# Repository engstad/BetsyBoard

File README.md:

# Experimental STM32L486 breakout board

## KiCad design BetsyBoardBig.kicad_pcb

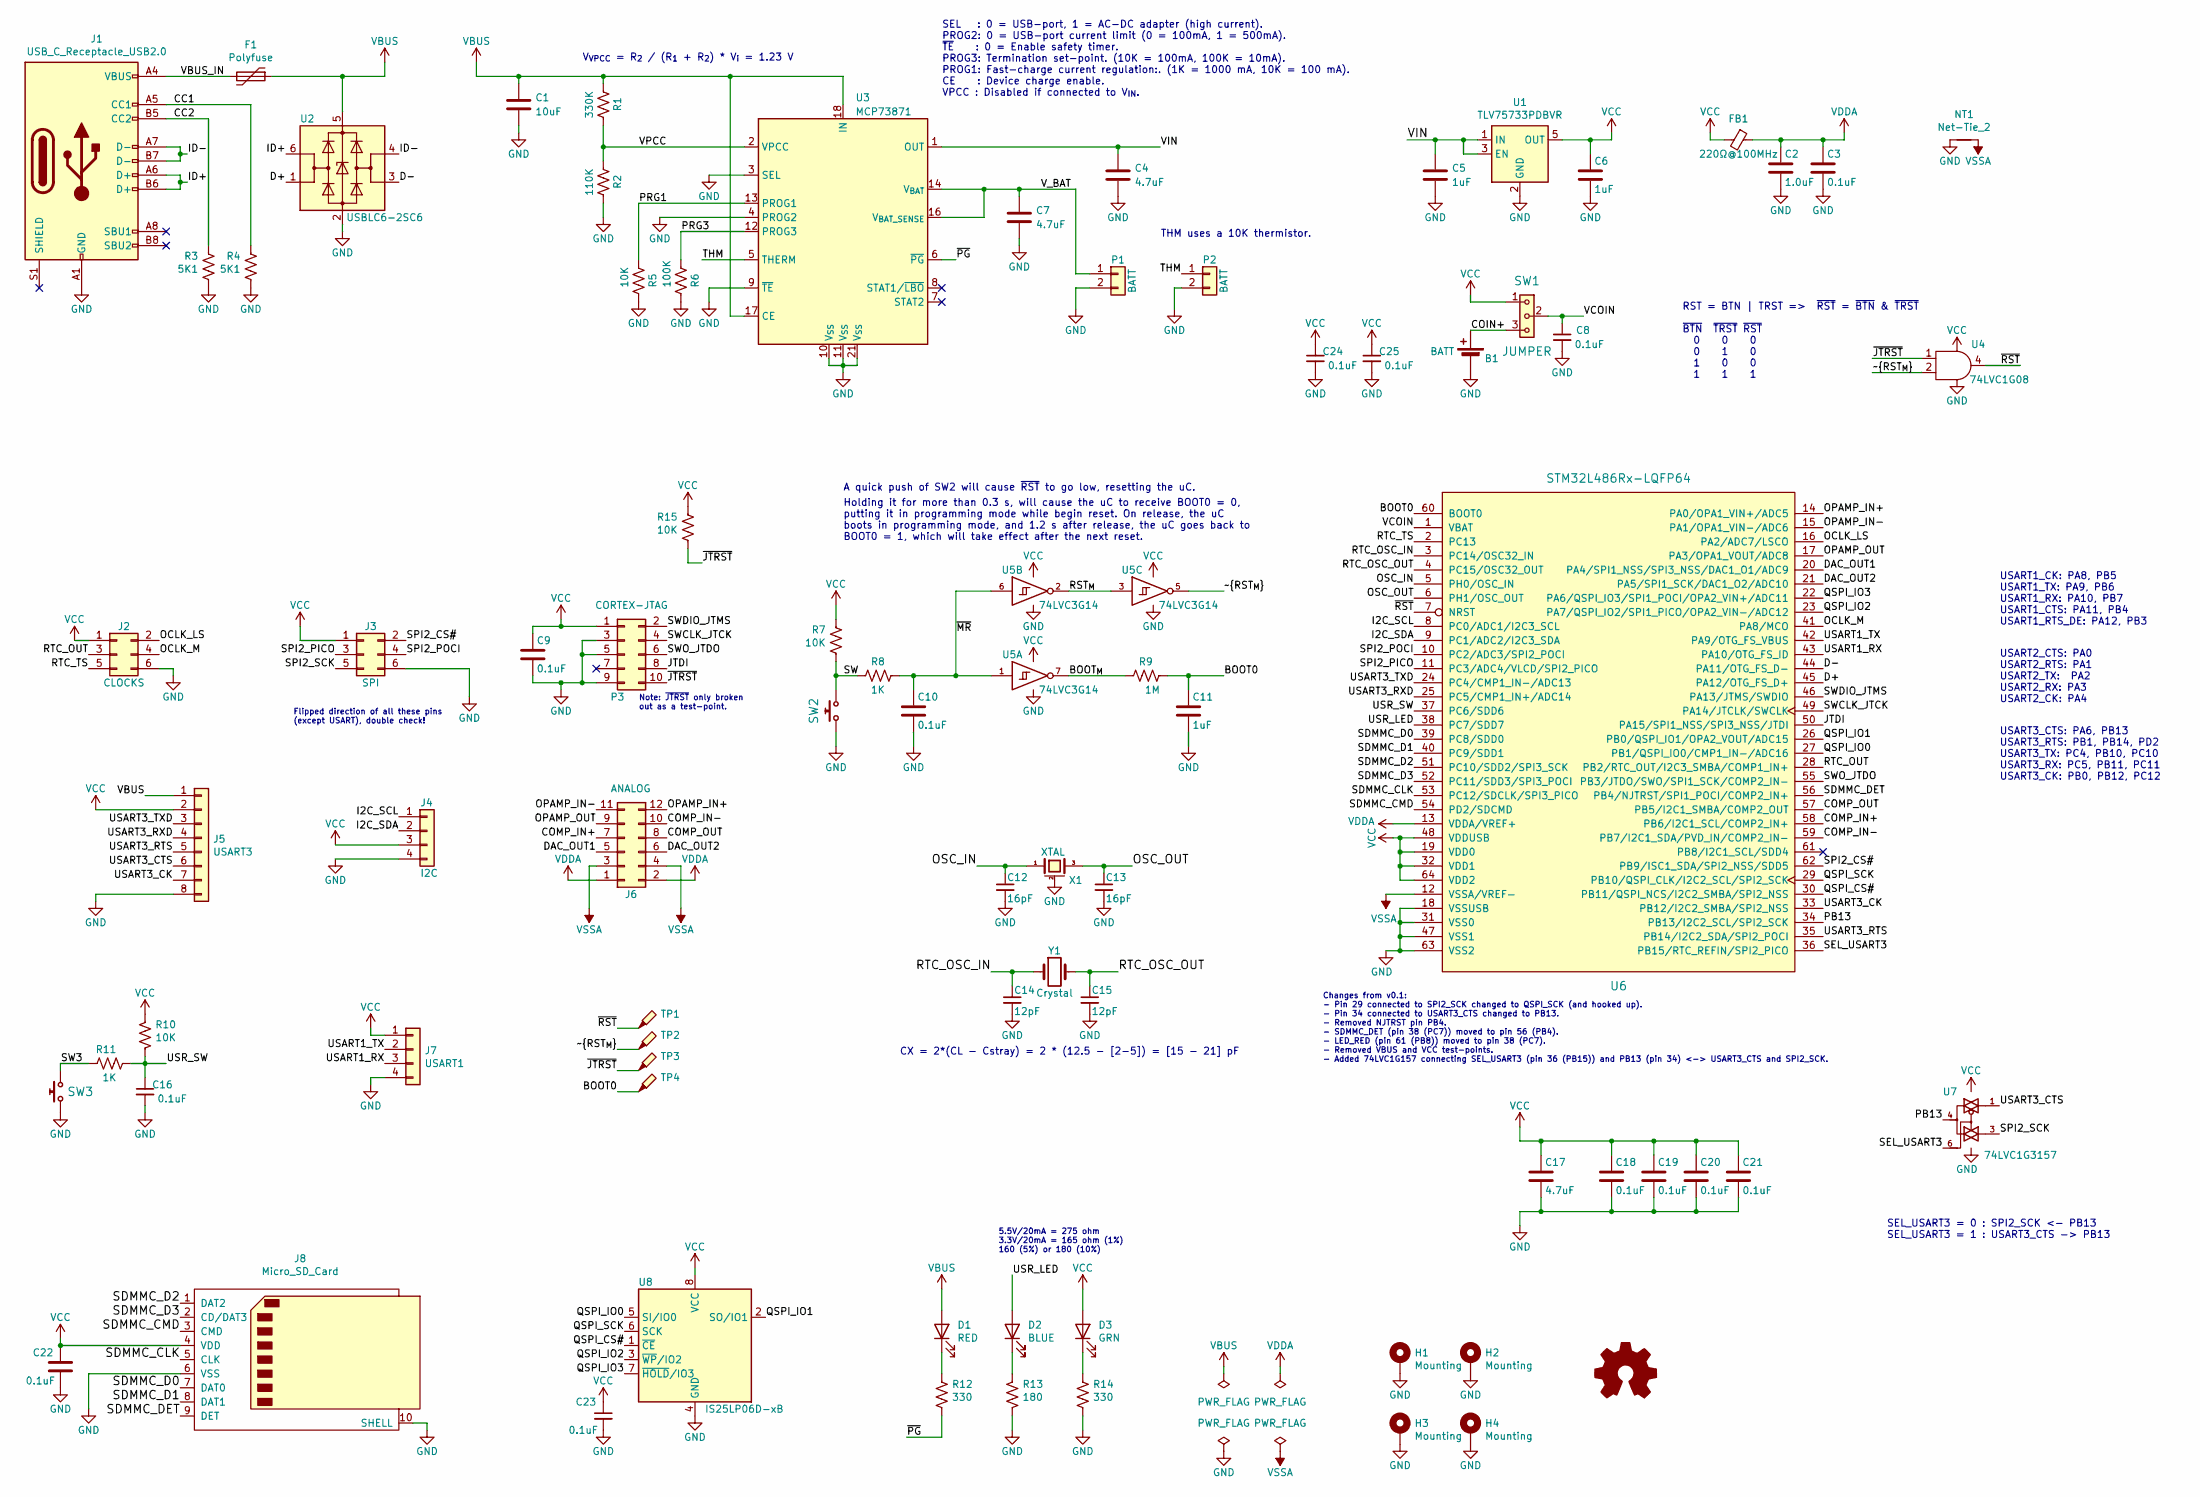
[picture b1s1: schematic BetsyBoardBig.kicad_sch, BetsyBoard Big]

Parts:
B1: BATT; Battery_Keystone_2894
C1: 10uF; C_0805_2012Metric
C2: 1.0uF; C_0805_2012Metric
C3, C8, C9, C10, C16, C18, C19, C20, C21, C22, C23, C24, C25: 0.1uF; C_0603_1608Metric
C4, C7, C17: 4.7uF; C_0805_2012Metric
C5, C6: 1uF; C_0805_2012Metric
C11: 1uF; C_0603_1608Metric
C12, C13: 16pF; C_0603_1608Metric
C14, C15: 12pF; C_0603_1608Metric
D1: RED; LED_0603_1608Metric
D2: BLUE; LED_0603_1608Metric
D3: GRN; LED_0603_1608Metric
F1: Polyfuse; Fuse_0805_2012Metric
FB1: 220Ω@100MHz; L_0805_2012Metric; Manuf # BLM21PG221SN1D
H1, H2, H3, H4: Mounting; MountingHole_3.2mm_M3_Pad_Via
J1: USB_C_Receptacle_USB2.0; USB_C_Receptacle_GCT_USB4085
J2: CLOCKS; PinHeader_2x03_P2.54mm_Vertical
J3: SPI; PinHeader_2x03_P2.54mm_Vertical
J4: I2C; JST_SH_SM04B-SRSS-TB_1x04-1MP_P1.00mm_Horizontal
J5: USART3; PinHeader_1x08_P2.54mm_Horizontal
J6: ANALOG; PinHeader_2x06_P2.54mm_Horizontal
J7: USART1; PinHeader_1x04_P2.54mm_Horizontal
J8: Micro_SD_Card; Molex_PS_105162_001; DigiKey# WM14405CT-ND
NT1: Net-Tie_2; NetTie-2_SMD_Pad0.5mm
P1: BATT; JST_PH_B2B-PH-K_1x02_P2.00mm_Vertical
P2: BATT; pin-socket-2
P3: CORTEX-JTAG; PinHeader_2x05_P1.27mm_Vertical
R1: 330K; R_0603_1608Metric
R2: 110K; R_0603_1608Metric
R3, R4: 5K1; R_0603_1608Metric
R5, R7, R10, R15: 10K; R_0603_1608Metric
R6: 100K; R_0603_1608Metric
R8, R11: 1K; R_0603_1608Metric
R9: 1M; R_0603_1608Metric
R12, R14: 330; R_0603_1608Metric
R13: 180; R_0603_1608Metric
SW1: JUMPER; PinHeader_1x03_P2.54mm_Vertical
SW2: TE-FSM4J; TACTILE_SWITCH-TE-FSM4JSMAATR
SW3: SW_PUSH_NO_ALT; TACTILE_SWITCH-TE-FSM4JSMAATR
TP1, TP2, TP3, TP4: TestPoint_Probe; TestPoint_Pad_1.0x1.0mm
U1: TLV75733PDBVR‎; SOT-23-5
U2: USBLC6-2SC6; SOT-23-6
U3: MCP73871; QFN-20-1EP_4x4mm_P0.5mm_EP2.5x2.5mm
U4: 74LVC1G08; SOT-23-5
U5: 74LVC3G14; SSOP-8_2.95x2.8mm_P0.65mm
U6: STM32L486Rx-LQFP64; LQFP-64_10x10mm_P0.5mm
U7: 74LVC1G3157; SOT-23-6
U8: IS25LP06D-xB; SOIC-8_5.275x5.275mm_P1.27mm
X1: XTAL; cstce-v-c
Y1: Crystal; Crystal_SMD_3215-2Pin_3.2x1.5mm

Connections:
/BOOT0: C11.1, R9.1, TP4.1, U6.60 (BOOT0)
/BOOT_{M}: R9.2, U5.7
/CC1: J1.A5 (CC1), R4.1
/CC2: J1.B5 (CC2), R3.1
/COIN+: B1.1 (+), SW1.3
/COMP_IN+: J6.7, U6.58 (PB6/I2C1_SCL/COMP2_IN+)
/COMP_IN-: J6.10, U6.59 (PB7/I2C1_SDA/PVD_IN/COMP2_IN-)
/COMP_OUT: J6.8, U6.57 (PB5/I2C1_SMBA/COMP2_OUT)
/D+: U2.1 (I/O1), U6.45 (PA12/OTG_FS_D+)
/D-: U2.3 (I/O2), U6.44 (PA11/OTG_FS_D-)
/DAC_OUT1: J6.5, U6.20 (PA4/SPI1_NSS/SPI3_NSS/DAC1_O1/ADC9)
/DAC_OUT2: J6.6, U6.21 (PA5/SPI1_SCK/DAC1_O2/ADC10)
/I2C_SCL: J4.1, U6.8 (PC0/ADC1/I2C3_SCL)
/I2C_SDA: J4.2, U6.9 (PC1/ADC2/I2C3_SDA)
/ID+: J1.A6 (D+), J1.B6 (D+), U2.6 (I/O1)
/ID-: J1.A7 (D-), J1.B7 (D-), U2.4 (I/O2)
/JTDI: P3.8, U6.50 (PA15/SPI1_NSS/SPI3_NSS/JTDI)
/OCLK_LS: J2.2, U6.16 (PA2/ADC7/LSCO)
/OCLK_M: J2.4, U6.41 (PA8/MCO)
/OPAMP_IN+: J6.12, U6.14 (PA0/OPA1_VIN+/ADC5)
/OPAMP_IN-: J6.11, U6.15 (PA1/OPA1_VIN-/ADC6)
/OPAMP_OUT: J6.9, U6.17 (PA3/OPA1_VOUT/ADC8)
/OSC_IN: C12.1, U6.5 (PH0/OSC_IN), X1.1
/OSC_OUT: C13.1, U6.6 (PH1/OSC_OUT), X1.3
/PB13: U6.34 (PB13/I2C2_SCL/SPI2_SCK), U7.4
/PRG1: R5.2, U3.13 (PROG1)
/PRG3: R6.2, U3.12 (PROG3)
/QSPI_CS#: U6.30 (PB11/QSPI_NCS/I2C2_SMBA/SPI2_NSS), U8.1 (~CE)
/QSPI_IO0: U6.27 (PB1/QSPI_IO0/CMP1_IN-/ADC16), U8.5 (SI/IO0)
/QSPI_IO1: U6.26 (PB0/QSPI_IO1/OPA2_VOUT/ADC15), U8.2 (SO/IO1)
/QSPI_IO2: U6.23 (PA7/QSPI_IO2/SPI1_PICO/OPA2_VIN-/ADC12), U8.3 (~WP/IO2)
/QSPI_IO3: U6.22 (PA6/QSPI_IO3/SPI1_POCI/OPA2_VIN+/ADC11), U8.7 (~HOLD/IO3)
/QSPI_SCK: U6.29 (PB10/QSPI_CLK/I2C2_SCL/SPI2_SCK), U8.6 (SCK)
/RST_{M}: U5.2, U5.3
/RTC_OSC_IN: C14.1, U6.3 (PC14/OSC32_IN), Y1.1
/RTC_OSC_OUT: C15.1, U6.4 (PC15/OSC32_OUT), Y1.2
/RTC_OUT: J2.3, U6.28 (PB2/RTC_OUT/I2C3_SMBA/COMP1_IN+)
/RTC_TS: J2.5, U6.2 (PC13)
/SDMMC_CLK: J8.5 (CLK), U6.53 (PC12/SDCLK/SPI3_PICO)
/SDMMC_CMD: J8.3 (CMD), U6.54 (PD2/SDCMD)
/SDMMC_D0: J8.7 (DAT0), U6.39 (PC8/SDD0)
/SDMMC_D1: J8.8 (DAT1), U6.40 (PC9/SDD1)
/SDMMC_D2: J8.1 (DAT2), U6.51 (PC10/SDD2/SPI3_SCK)
/SDMMC_D3: J8.2 (CD/DAT3), U6.52 (PC11/SDD3/SPI3_POCI)
/SDMMC_DET: J8.9 (DET), U6.56 (PB4/NJTRST/SPI1_POCI/COMP2_IN+)
/SEL_USART3: U6.36 (PB15/RTC_REFIN/SPI2_PICO), U7.6
/SPI2_CS#: J3.2, U6.62 (PB9/ISC1_SDA/SPI2_NSS/SDD5)
/SPI2_PICO: J3.3, U6.11 (PC3/ADC4/VLCD/SPI2_PICO)
/SPI2_POCI: J3.4, U6.10 (PC2/ADC3/SPI2_POCI)
/SPI2_SCK: J3.5, U7.3
/SW: R7.2, R8.2, SW2.2
/SW3: R11.2, SW3.2
/SWCLK_JTCK: P3.4, U6.49 (PA14/JTCLK/SWCLK)
/SWDIO_JTMS: P3.2, U6.46 (PA13/JTMS/SWDIO)
/SWO_JTDO: P3.6, U6.55 (PB3/JTDO/SWO/SPI1_SCK/COMP2_IN-)
/THM: P2.1, U3.5 (THERM)
/USART1_RX: J7.3, U6.43 (PA10/OTG_FS_ID)
/USART1_TX: J7.2, U6.42 (PA9/OTG_FS_VBUS)
/USART3_CK: J5.7, U6.33 (PB12/I2C2_SMBA/SPI2_NSS)
/USART3_CTS: J5.6, U7.1
/USART3_RTS: J5.5, U6.35 (PB14/I2C2_SDA/SPI2_POCI)
/USART3_RXD: J5.4, U6.25 (PC5/CMP1_IN+/ADC14)
/USART3_TXD: J5.3, U6.24 (PC4/CMP1_IN-/ADC13)
/USR_LED: D2.2 (A), U6.38 (PC7/SDD7)
/USR_SW: C16.1, R10.2, R11.1, U6.37 (PC6/SDD6)
/VBUS_IN: F1.2, J1.A4 (VBUS), J1.A9 (VBUS), J1.B4 (VBUS), J1.B9 (VBUS)
/VCOIN: C8.1, SW1.2, U6.1 (VBAT)
/VIN: C4.1, C5.1, U1.1 (IN), U1.3 (EN), U3.1 (OUT), U3.20 (OUT)
/VPCC: R1.1, R2.2, U3.2 (VPCC)
/V_BAT: C7.1, P1.1, U3.14 (V_{BAT}), U3.15 (V_{BAT}), U3.16 (V_{BAT_SENSE})
/~JTRST: P3.10, R15.2, TP3.1, U4.1
/~MR: C10.1, R8.1, U5.1, U5.6
/~PG: R12.2, U3.6 (~PG)
/~RST_{M}: TP2.1, U4.2, U5.5
/~RST: TP1.1, U4.4, U6.7 (NRST)
GND: B1.2 (-), C1.2, C2.2, C3.2, C4.2, C5.2, C6.2, C7.2, C8.2, C9.2, C10.2, C11.2, C12.2, C13.2, C14.2, C15.2, C16.2, C17.2, C18.2, C19.2, C20.2, C21.2, C22.2, C23.2, C24.2, C25.2, H1.1, H2.1, H3.1, H4.1, J1.A1 (GND), J1.A12 (GND), J1.B1 (GND), J1.B12 (GND), J2.6, J3.6, J4.4, J5.8, J7.4, J8.6 (VSS), J8.10 (SHELL), NT1.1, P1.2, P2.2, P3.3, P3.5, P3.9, R2.1, R3.2, R4.2, R5.1, R6.1, R13.2, R14.2, SW2.1, SW3.1, U1.2 (GND), U2.2 (GND), U3.3 (SEL), U3.4 (PROG2), U3.9 (~TE), U3.10 (V_{SS}), U3.11 (V_{SS}), U3.21 (V_{SS}), U4.3 (GND), U5.4 (GND), U6.18 (VSSUSB), U6.31 (VSS0), U6.47 (VSS1), U6.63 (VSS2), U7.2 (GND), U8.4 (GND), X1.2 (gnd)
unnamed: D1.1 (K), R12.1
unnamed: D2.1 (K), R13.1
unnamed: D3.1 (K), R14.1
VBUS: C1.1, D1.2 (A), F1.1, J5.1, R1.2, U2.5 (VBUS), U3.17 (CE), U3.18 (IN), U3.19 (IN)
VCC: C6.1, C9.1, C17.1, C18.1, C19.1, C20.1, C21.1, C22.1, C23.1, C24.1, C25.1, D3.2 (A), FB1.2, J2.1, J3.1, J4.3, J5.2, J7.1, J8.4 (VDD), P3.1, R7.1, R10.1, R15.1, SW1.1, U1.5 (OUT), U4.5 (VCC), U5.8 (VCC), U6.19 (VDD0), U6.32 (VDD1), U6.48 (VDDUSB), U6.64 (VDD2), U7.5 (VCC), U8.8 (VCC)
VDDA: C2.1, C3.1, FB1.1, J6.1, J6.2, U6.13 (VDDA/VREF+)
VSSA: J6.3, J6.4, NT1.2, U6.12 (VSSA/VREF-)

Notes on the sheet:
A quick push of SW2 will cause ~{RST} to go low, resetting the uC.
Note: ~{JTRST} only broken out as a test-point.
RST = BTN | TRST => ~{RST} = ~{BTN} & ~{TRST} ~{BTN} ~{TRST} ~{RST} 0 0 0 0 1 0 1 0 0 1 1 1
USART2_CTS: PA0 USART2_RTS: PA1 USART2_TX: PA2 USART2_RX: PA3 USART2_CK: PA4
Holding it for more than 0.3 s, will cause the uC to receive BOOT0 = 0, putting it in programming mode while begin reset. On release, the uC boots in programming mode, and 1.2 s after release, the uC goes back to BOOT0 = 1, which will take effect after the next reset.
Flipped direction of all these pins (except USART), double check!
THM uses a 10K thermistor.
CX = 2*(CL - Cstray) = 2 * (12.5 - [2-5]) = [15 - 21] pF
V_{VPCC} = R_{2} / (R_{1} + R_{2}) * V_{i} = 1.23 V
USART1_CK: PA8, PB5 USART1_TX: PA9, PB6 USART1_RX: PA10, PB7 USART1_CTS: PA11, PB4 USART1_RTS_DE: PA12, PB3
USART3_CTS: PA6, PB13 USART3_RTS: PB1, PB14, PD2 USART3_TX: PC4, PB10, PC10 USART3_RX: PC5, PB11, PC11 USART3_CK: PB0, PB12, PC12
SEL_USART3 = 0 : SPI2_SCK <- PB13 SEL_USART3 = 1 : USART3_CTS -> PB13
SEL : 0 = USB-port, 1 = AC-DC adapter (high current). PROG2: 0 = USB-port current limit (0 = 100mA, 1 = 500mA). ~{TE} : 0 = Enable safety timer. PROG3: Termination set-point. (10K = 100mA, 100K = 10mA). PROG1: Fast-charge current regulation:. (1K = 1000 mA, 10K = 100 mA). CE : Device charge enable.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
5.5V/20mA = 275 ohm 3.3V/20mA = 165 ohm (1%) 160 (5%) or 180 (10%)
Changes from v0.1: - Pin 29 connected to SPI2_SCK changed to QSPI_SCK (and hooked up). - Pin 34 connected to USART3_CTS changed to PB13. - Removed NJTRST pin PB4. - SDMMC_DET (pin 38 (PC7)) moved to pin 56 (PB4). - LED_RED (pin 61 (PB8)) moved to pin 38 (PC7). - Removed VBUS and VCC test-points. - 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

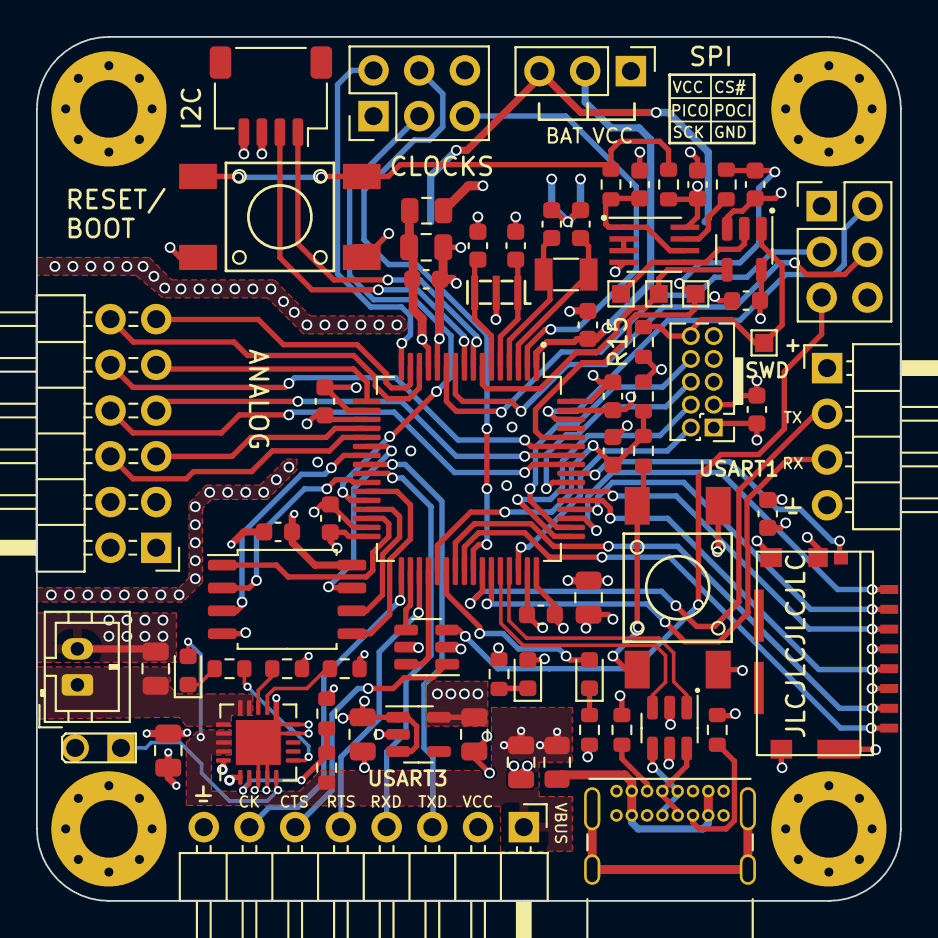
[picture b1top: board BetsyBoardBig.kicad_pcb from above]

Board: 4 copper layers, 48.0 x 48.0 mm, 79 parts (1 on the bottom side), 83 nets.

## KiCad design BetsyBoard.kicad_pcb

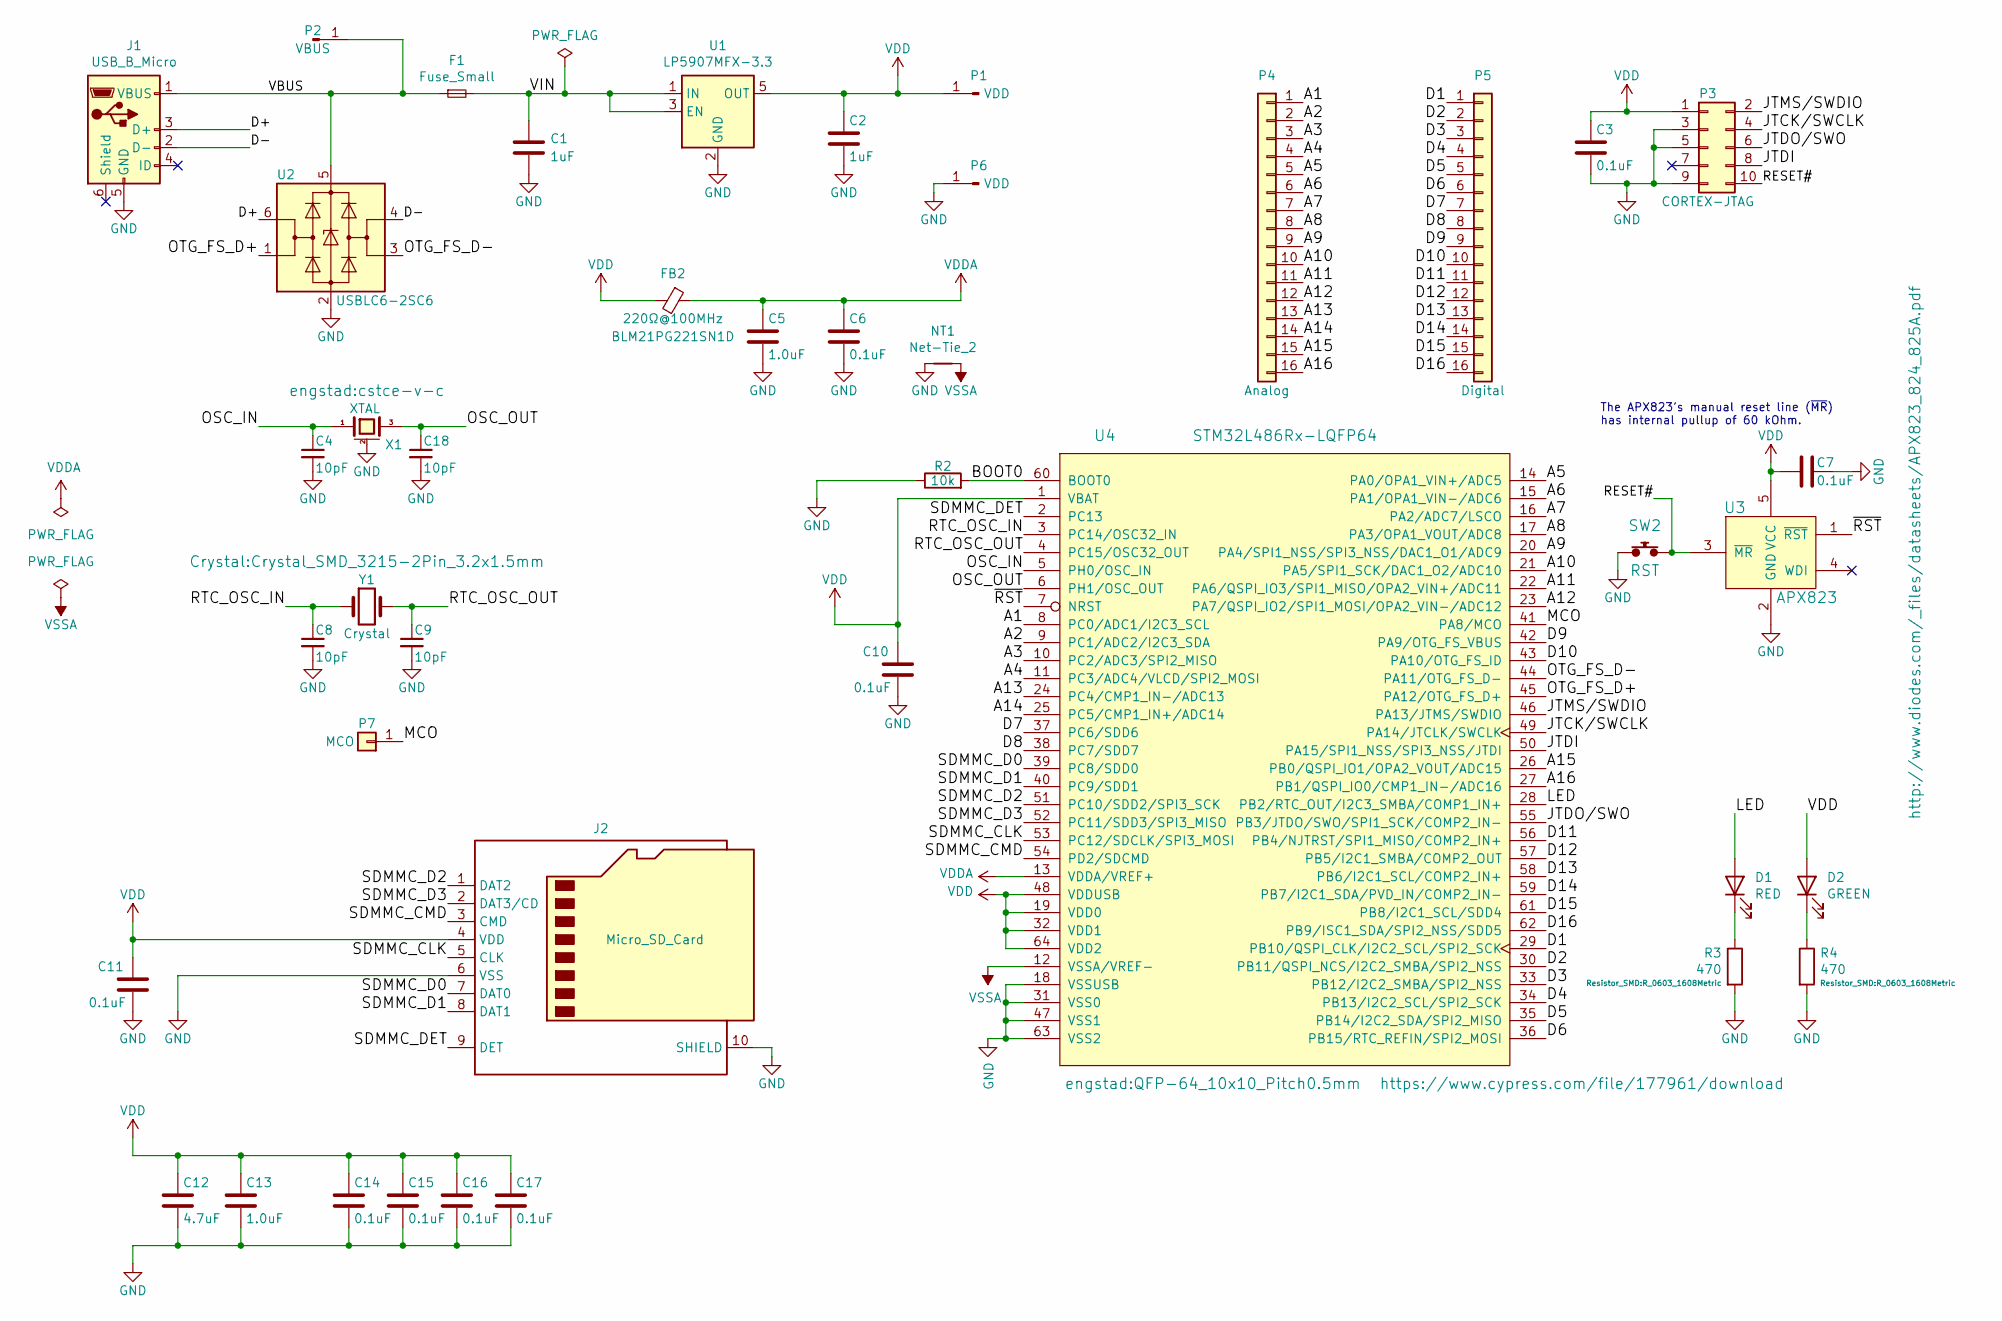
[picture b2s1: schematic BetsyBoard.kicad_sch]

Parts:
C1, C2: 1uF; C_0805_2012Metric
C3, C6, C7, C10, C11, C14, C15, C16, C17: 0.1uF; C_0603_1608Metric
C4, C8, C9, C18: 10pF; C_0603_1608Metric
C5: 1.0uF; C_0603_1608Metric
C12: 4.7uF; C_0805_2012Metric
C13: 1.0uF; C_0805_2012Metric
D1: RED; LED_0603_1608Metric
D2: GREEN; LED_0603_1608Metric
F1: Fuse_Small; Fuse_0805_2012Metric
FB2: 220Ω@100MHz; L_0805_2012Metric; Manuf # BLM21PG221SN1D
J1: USB_B_Micro; usb-micro-b-amphenol-fci-10118194-oval
J2: Micro_SD_Card; Molex_PS_105162_001
NT1: Net-Tie_2; net-tie-0.4mm
P1: VDD; pin-strip-1
P2: VBUS; pin-strip-1
P3: CORTEX-JTAG; conn-jtag-0.05; Mouser# 200-FTSH10501LDV007K
P4: Analog; pin-strip-16
P5: Digital; pin-strip-16
P6: VDD; PinHeader_1x01_P2.54mm_Vertical
P7: MCO; pin-socket-1
R2: 10k; R_0603_1608Metric
R3, R4: 470; R_0603_1608Metric
SW2: RST; tactile-switch-evpay-34x29mm
U1: LP5907MFX-3.3; SOT-23-5
U2: USBLC6-2SC6; SOT-23-6
U3: APX823; SOT-23-5
U4: STM32L486Rx-LQFP64; QFP-64_10x10_Pitch0.5mm
X1: XTAL; cstce-v-c
Y1: Crystal; Crystal_SMD_3215-2Pin_3.2x1.5mm

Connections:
/A1: P4.1, U4.8 (PC0/ADC1/I2C3_SCL)
/A2: P4.2, U4.9 (PC1/ADC2/I2C3_SDA)
/A3: P4.3, U4.10 (PC2/ADC3/SPI2_MISO)
/A4: P4.4, U4.11 (PC3/ADC4/VLCD/SPI2_MOSI)
/A5: P4.5, U4.14 (PA0/OPA1_VIN+/ADC5)
/A6: P4.6, U4.15 (PA1/OPA1_VIN-/ADC6)
/A7: P4.7, U4.16 (PA2/ADC7/LSCO)
/A8: P4.8, U4.17 (PA3/OPA1_VOUT/ADC8)
/A9: P4.9, U4.20 (PA4/SPI1_NSS/SPI3_NSS/DAC1_O1/ADC9)
/A10: P4.10, U4.21 (PA5/SPI1_SCK/DAC1_O2/ADC10)
/A11: P4.11, U4.22 (PA6/QSPI_IO3/SPI1_MISO/OPA2_VIN+/ADC11)
/A12: P4.12, U4.23 (PA7/QSPI_IO2/SPI1_MOSI/OPA2_VIN-/ADC12)
/A13: P4.13, U4.24 (PC4/CMP1_IN-/ADC13)
/A14: P4.14, U4.25 (PC5/CMP1_IN+/ADC14)
/A15: P4.15, U4.26 (PB0/QSPI_IO1/OPA2_VOUT/ADC15)
/A16: P4.16, U4.27 (PB1/QSPI_IO0/CMP1_IN-/ADC16)
/BOOT0: R2.2, U4.60 (BOOT0)
/D1: P5.1, U4.29 (PB10/QSPI_CLK/I2C2_SCL/SPI2_SCK)
/D2: P5.2, U4.30 (PB11/QSPI_NCS/I2C2_SMBA/SPI2_NSS)
/D3: P5.3, U4.33 (PB12/I2C2_SMBA/SPI2_NSS)
/D4: P5.4, U4.34 (PB13/I2C2_SCL/SPI2_SCK)
/D5: P5.5, U4.35 (PB14/I2C2_SDA/SPI2_MISO)
/D6: P5.6, U4.36 (PB15/RTC_REFIN/SPI2_MOSI)
/D7: P5.7, U4.37 (PC6/SDD6)
/D8: P5.8, U4.38 (PC7/SDD7)
/D9: P5.9, U4.42 (PA9/OTG_FS_VBUS)
/D10: P5.10, U4.43 (PA10/OTG_FS_ID)
/D11: P5.11, U4.56 (PB4/NJTRST/SPI1_MISO/COMP2_IN+)
/D12: P5.12, U4.57 (PB5/I2C1_SMBA/COMP2_OUT)
/D13: P5.13, U4.58 (PB6/I2C1_SCL/COMP2_IN+)
/D14: P5.14, U4.59 (PB7/I2C1_SDA/PVD_IN/COMP2_IN-)
/D15: P5.15, U4.61 (PB8/I2C1_SCL/SDD4)
/D16: P5.16, U4.62 (PB9/ISC1_SDA/SPI2_NSS/SDD5)
/D+: J1.3 (D+), U2.6 (I/O1)
/D-: J1.2 (D-), U2.4 (I/O2)
/JTCK/SWCLK: P3.4, U4.49 (PA14/JTCLK/SWCLK)
/JTDI: P3.8, U4.50 (PA15/SPI1_NSS/SPI3_NSS/JTDI)
/JTDO/SWO: P3.6, U4.55 (PB3/JTDO/SWO/SPI1_SCK/COMP2_IN-)
/JTMS/SWDIO: P3.2, U4.46 (PA13/JTMS/SWDIO)
/LED: D1.2 (A), U4.28 (PB2/RTC_OUT/I2C3_SMBA/COMP1_IN+)
/MCO: P7.1, U4.41 (PA8/MCO)
/OSC_IN: C4.1, U4.5 (PH0/OSC_IN), X1.1
/OSC_OUT: C18.1, U4.6 (PH1/OSC_OUT), X1.3
/OTG_FS_D+: U2.1 (I/O1), U4.45 (PA12/OTG_FS_D+)
/OTG_FS_D-: U2.3 (I/O2), U4.44 (PA11/OTG_FS_D-)
/RESET#: P3.10, SW2.2, U3.3 (~MR)
/RTC_OSC_IN: C8.1, U4.3 (PC14/OSC32_IN), Y1.1
/RTC_OSC_OUT: C9.1, U4.4 (PC15/OSC32_OUT), Y1.2
/SDMMC_CLK: J2.5 (CLK), U4.53 (PC12/SDCLK/SPI3_MOSI)
/SDMMC_CMD: J2.3 (CMD), U4.54 (PD2/SDCMD)
/SDMMC_D0: J2.7 (DAT0), U4.39 (PC8/SDD0)
/SDMMC_D1: J2.8 (DAT1), U4.40 (PC9/SDD1)
/SDMMC_D2: J2.1 (DAT2), U4.51 (PC10/SDD2/SPI3_SCK)
/SDMMC_D3: J2.2 (DAT3/CD), U4.52 (PC11/SDD3/SPI3_MISO)
/SDMMC_DET: J2.9 (DET), U4.2 (PC13)
/VBUS: F1.1, J1.1 (VBUS), P2.1, U2.5 (VBUS)
/VIN: C1.1, F1.2, U1.1 (IN), U1.3 (EN)
/~RST: U3.1 (~RST), U4.7 (NRST)
GND: C1.2, C2.2, C3.2, C4.2, C5.2, C6.2, C7.1, C8.2, C9.2, C10.2, C11.2, C12.2, C13.2, C14.2, C15.2, C16.2, C17.2, C18.2, J1.5 (GND), J2.6 (VSS), J2.10 (SHIELD), NT1.1, P3.3, P3.5, P3.9, P6.1, R2.1, R3.2, R4.2, SW2.1, U1.2 (GND), U2.2 (GND), U3.2 (GND), U4.18 (VSSUSB), U4.31 (VSS0), U4.47 (VSS1), U4.63 (VSS2), X1.2 (gnd)
unnamed: D1.1 (K), R3.1
unnamed: D2.1 (K), R4.1
VDD: C2.1, C3.1, C7.2, C10.1, C11.1, C12.1, C13.1, C14.1, C15.1, C16.1, C17.1, D2.2 (A), FB2.2, J2.4 (VDD), P1.1, P3.1, U1.5 (OUT), U3.5 (VCC), U4.1 (VBAT), U4.19 (VDD0), U4.32 (VDD1), U4.48 (VDDUSB), U4.64 (VDD2)
VDDA: C5.1, C6.1, FB2.1, U4.13 (VDDA/VREF+)
VSSA: NT1.2, U4.12 (VSSA/VREF-)

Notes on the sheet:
The APX823's manual reset line (~{MR}) has internal pullup of 60 kOhm.

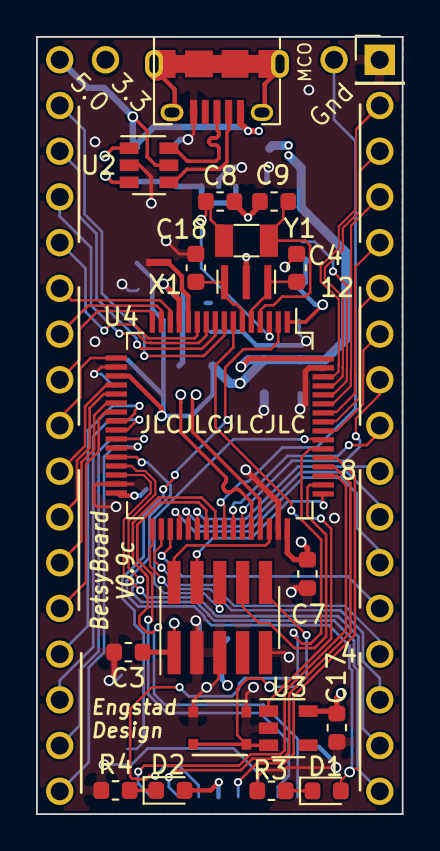
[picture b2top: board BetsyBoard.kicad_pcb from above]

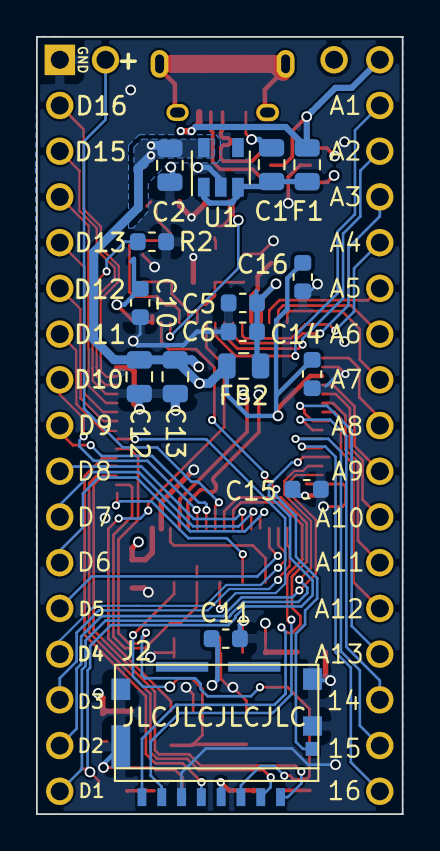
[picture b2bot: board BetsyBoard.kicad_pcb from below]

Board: 4 copper layers, 20.3 x 43.2 mm, 42 parts (18 on the bottom side), 64 nets.

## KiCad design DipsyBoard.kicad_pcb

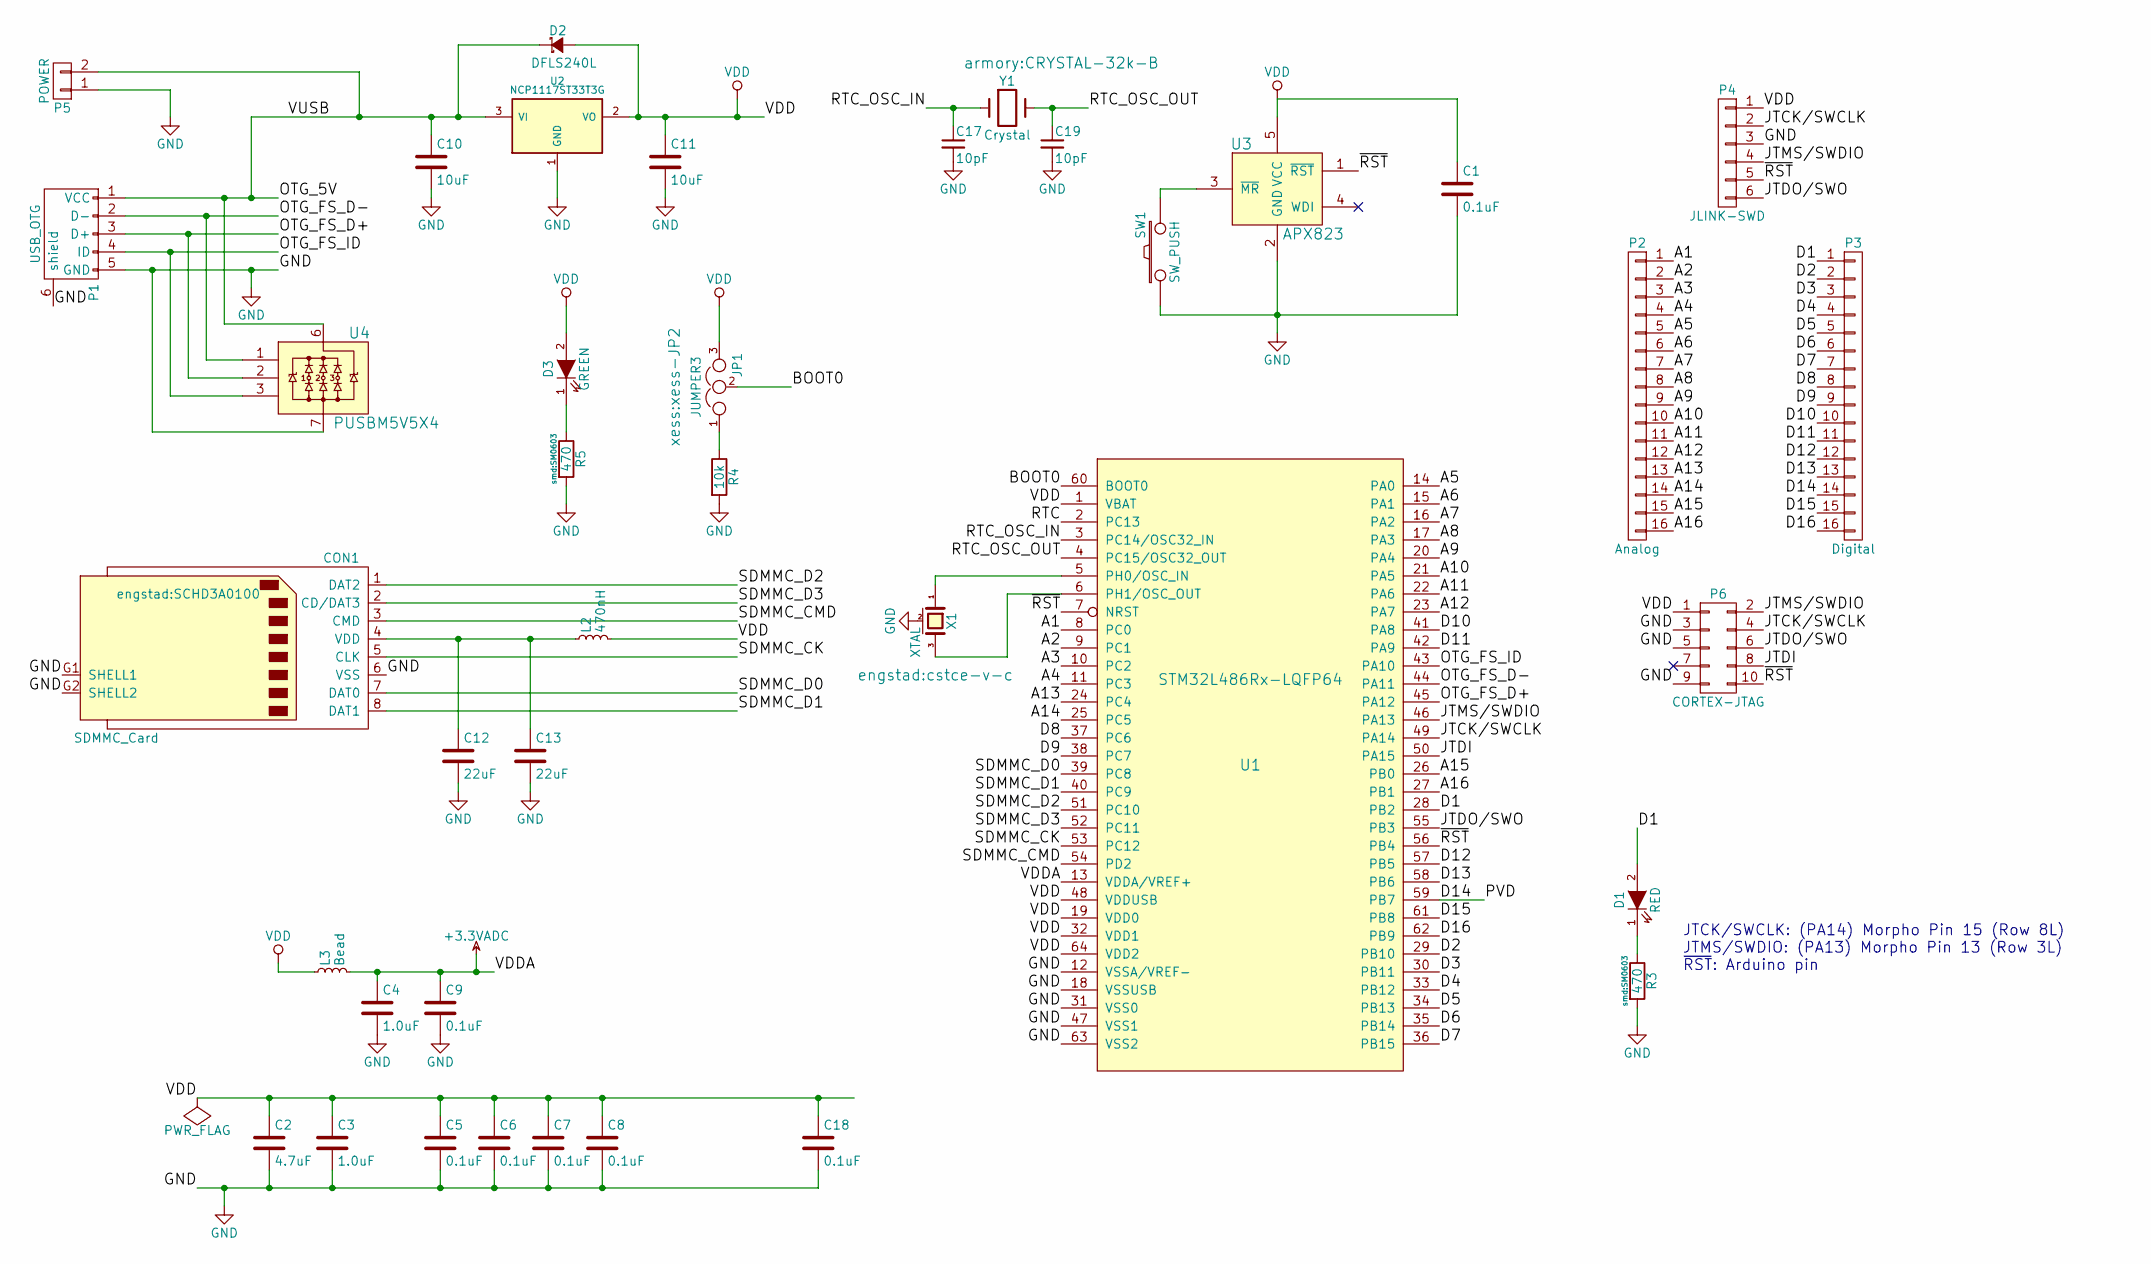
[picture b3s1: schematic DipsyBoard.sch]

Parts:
C1, C5, C6, C7, C8, C9, C18: 0.1uF; SM0603
C2: 4.7uF; SM0805
C3, C4: 1.0uF; SM0603
C10, C11: 10uF; SM0805
C12, C13: 22uF; SM1206
C17, C19: 10pF; SM0603
CON1: SDMMC_Card; SCHD3A0100
D1: RED; LED-0805
D2: DFLS240L; diode-smd-powerdi-123
D3: GREEN; LED-0805
JP1: JUMPER3; xess-JP2
L2: 470nH; SM0603
L3: Bead; SM0805; Manuf # BLM21PG221SN1D
P1: USB_OTG; usb-otg-short
P2: Analog; Pin_Header_Straight_1x16
P3: Digital; Pin_Header_Straight_1x16
P4: JLINK-SWD; HDR_1x6
P5: POWER; pin_socket_2
P6: CORTEX-JTAG; smt-pin-header-02x05-127
R3, R5: 470; SM0603
R4: 10k; SM0603
SW1: SW_PUSH; tactile-switch-te-147873-2
U1: STM32L486Rx-LQFP64; LQFP-64_10x10mm_Pitch0.5mm
U2: NCP1117ST33T3G; SOT-223
U3: APX823; SOT-23-5
U4: PUSBM5V5X4; dfn1616-6
X1: XTAL; cstce-v-c
Y1: Crystal; CRYSTAL-32k-B

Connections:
+3.3VADC: C4.1, C9.1, L3.2, U1.13 (VDDA/VREF+)
/A1: P2.1, U1.8 (PC0)
/A2: P2.2, U1.9 (PC1)
/A3: P2.3, U1.10 (PC2)
/A4: P2.4, U1.11 (PC3)
/A5: P2.5, U1.14 (PA0)
/A6: P2.6, U1.15 (PA1)
/A7: P2.7, U1.16 (PA2)
/A8: P2.8, U1.17 (PA3)
/A9: P2.9, U1.20 (PA4)
/A10: P2.10, U1.21 (PA5)
/A11: P2.11, U1.22 (PA6)
/A12: P2.12, U1.23 (PA7)
/A13: P2.13, U1.24 (PC4)
/A14: P2.14, U1.25 (PC5)
/A15: P2.15, U1.26 (PB0)
/A16: P2.16, U1.27 (PB1)
/BOOT0: JP1.2, U1.60 (BOOT0)
/D1: D1.2 (A), P3.1, U1.28 (PB2)
/D2: P3.2, U1.29 (PB10)
/D3: P3.3, U1.30 (PB11)
/D4: P3.4, U1.33 (PB12)
/D5: P3.5, U1.34 (PB13)
/D6: P3.6, U1.35 (PB14)
/D7: P3.7, U1.36 (PB15)
/D8: P3.8, U1.37 (PC6)
/D9: P3.9, U1.38 (PC7)
/D10: P3.10, U1.41 (PA8)
/D11: P3.11, U1.42 (PA9)
/D12: P3.12, U1.57 (PB5)
/D13: P3.13, U1.58 (PB6)
/D14: P3.14, U1.59 (PB7)
/D15: P3.15, U1.61 (PB8)
/D16: P3.16, U1.62 (PB9)
/JTCK/SWCLK: P4.2, P6.4, U1.49 (PA14)
/JTDI: P6.8, U1.50 (PA15)
/JTDO/SWO: P4.6, P6.6, U1.55 (PB3)
/JTMS/SWDIO: P4.4, P6.2, U1.46 (PA13)
/OTG_5V: C10.1, D2.1 (K), P1.1 (VCC), P5.2, U2.3 (VI), U4.6
/OTG_FS_D+: P1.3 (D+), U1.45 (PA12), U4.2
/OTG_FS_D-: P1.2 (D-), U1.44 (PA11), U4.1
/OTG_FS_ID: P1.4 (ID), U1.43 (PA10), U4.3
/RTC: U1.2 (PC13)
/RTC_OSC_IN: C17.1, U1.3 (PC14/OSC32_IN), Y1.1
/RTC_OSC_OUT: C19.1, U1.4 (PC15/OSC32_OUT), Y1.2
/SDMMC_CK: CON1.5 (CLK), U1.53 (PC12)
/SDMMC_CMD: CON1.3 (CMD), U1.54 (PD2)
/SDMMC_D0: CON1.7 (DAT0), U1.39 (PC8)
/SDMMC_D1: CON1.8 (DAT1), U1.40 (PC9)
/SDMMC_D2: CON1.1 (DAT2), U1.51 (PC10)
/SDMMC_D3: CON1.2 (CD/DAT3), U1.52 (PC11)
/~RST: P4.5, P6.10, U1.7 (NRST), U1.56 (PB4), U3.1 (~RST~)
GND: C1.2, C2.2, C3.2, C4.2, C5.2, C6.2, C7.2, C8.2, C9.2, C10.2, C11.2, C12.2, C13.2, C17.2, C18.2, C19.2, CON1.6 (VSS), CON1.G1 (SHELL1), CON1.G2 (SHELL2), P1.5 (GND), P1.6 (shield), P4.3, P5.1, P6.3, P6.5, P6.9, R3.2, R4.2, R5.2, SW1.1, U1.12 (VSSA/VREF-), U1.18 (VSSUSB), U1.31 (VSS0), U1.47 (VSS1), U1.63 (VSS2), U2.1 (GND), U3.2 (GND), U4.7, X1.2 (gnd)
unnamed: C12.1, C13.1, CON1.4 (VDD), L2.1
unnamed: D1.1 (K), R3.1
unnamed: D3.1 (K), R5.1
unnamed: JP1.1, R4.1
unnamed: SW1.2, U3.3 (~MR~)
unnamed: U1.5 (PH0/OSC_IN), X1.1
unnamed: U1.6 (PH1/OSC_OUT), X1.3
VDD: C1.1, C2.1, C3.1, C5.1, C6.1, C7.1, C8.1, C11.1, C18.1, D2.2 (A), D3.2 (A), JP1.3, L2.2, L3.1, P4.1, P6.1, U1.1 (VBAT), U1.19 (VDD0), U1.32 (VDD1), U1.48 (VDDUSB), U1.64 (VDD2), U2.2 (VO), U3.5 (VCC)

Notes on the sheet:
JTCK/SWCLK: (PA14) Morpho Pin 15 (Row 8L) JTMS/SWDIO: (PA13) Morpho Pin 13 (Row 3L) ~RST~: Arduino pin

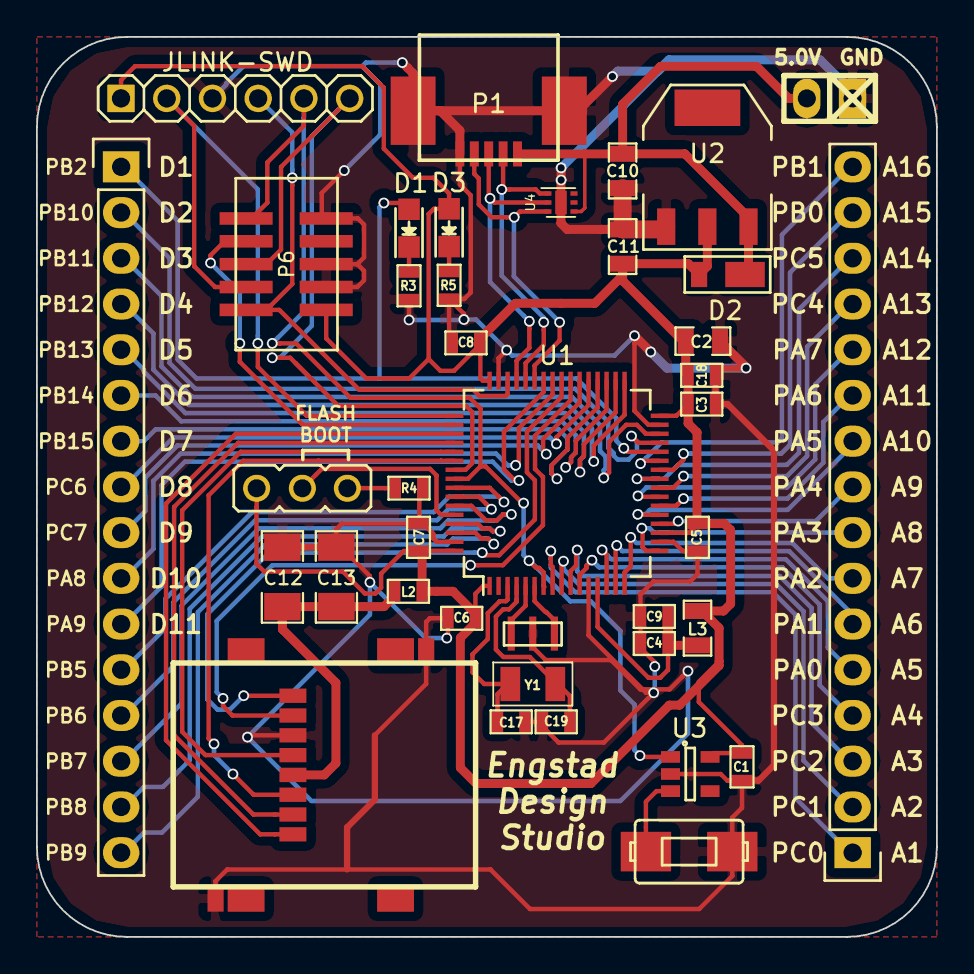
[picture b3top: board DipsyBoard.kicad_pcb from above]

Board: 2 copper layers, 50.0 x 50.0 mm, 39 parts (0 on the bottom side), 60 nets.

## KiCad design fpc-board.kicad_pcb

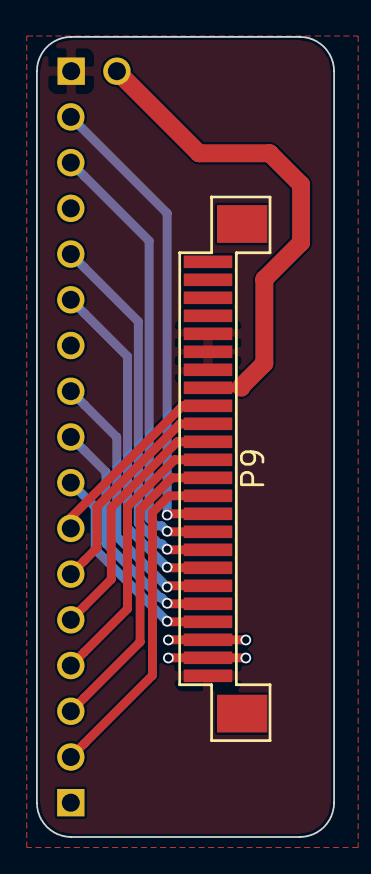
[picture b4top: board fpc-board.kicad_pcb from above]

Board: 4 copper layers, 16.5 x 44.4 mm, 3 parts (0 on the bottom side), 15 nets.

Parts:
P9: CONN_01X24; fpc-24-1.0mm
P10: Digital; pin-strip-16
P11: BATT; pin-socket-2

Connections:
/D2: P9.11, P10.2
/D3: P9.12, P10.3
/D4: P9.13, P10.4
/D5: P9.14, P10.5
/D6: P9.15, P10.6
/D7: P9.16, P10.7
/D8: P9.4, P10.8
/D9: P9.5, P10.9
/D10: P9.6, P10.10
/D12: P9.7, P10.12
/D13: P9.8, P10.13
/D15: P9.9, P10.15
/D16: P9.10, P10.16
GND: P9.1, P9.18, P9.19, P9.20, P11.1
VDD: P9.2, P9.3, P9.17, P11.2
